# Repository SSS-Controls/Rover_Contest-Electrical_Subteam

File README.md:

# Rover_Contest-Electrical_Subteam
This repo is for the purpose of developing the rover for the UC Davis Space and Satellite Systems Club's participation in the URC rover contest

## Downloading KiCAD
We are currently using *Kicad 10* which (as of the time of this writing) can be found at this link
https://www.kicad.org/download/
**DO NOT USE PREVIOUS VERSIONS. IF YOU DO IT MAY BREAK ALL OF THE WORK YOU DO.**

You'll be able to see the version of KiCAD on the top of the Window (Linux Mint example picture shown)

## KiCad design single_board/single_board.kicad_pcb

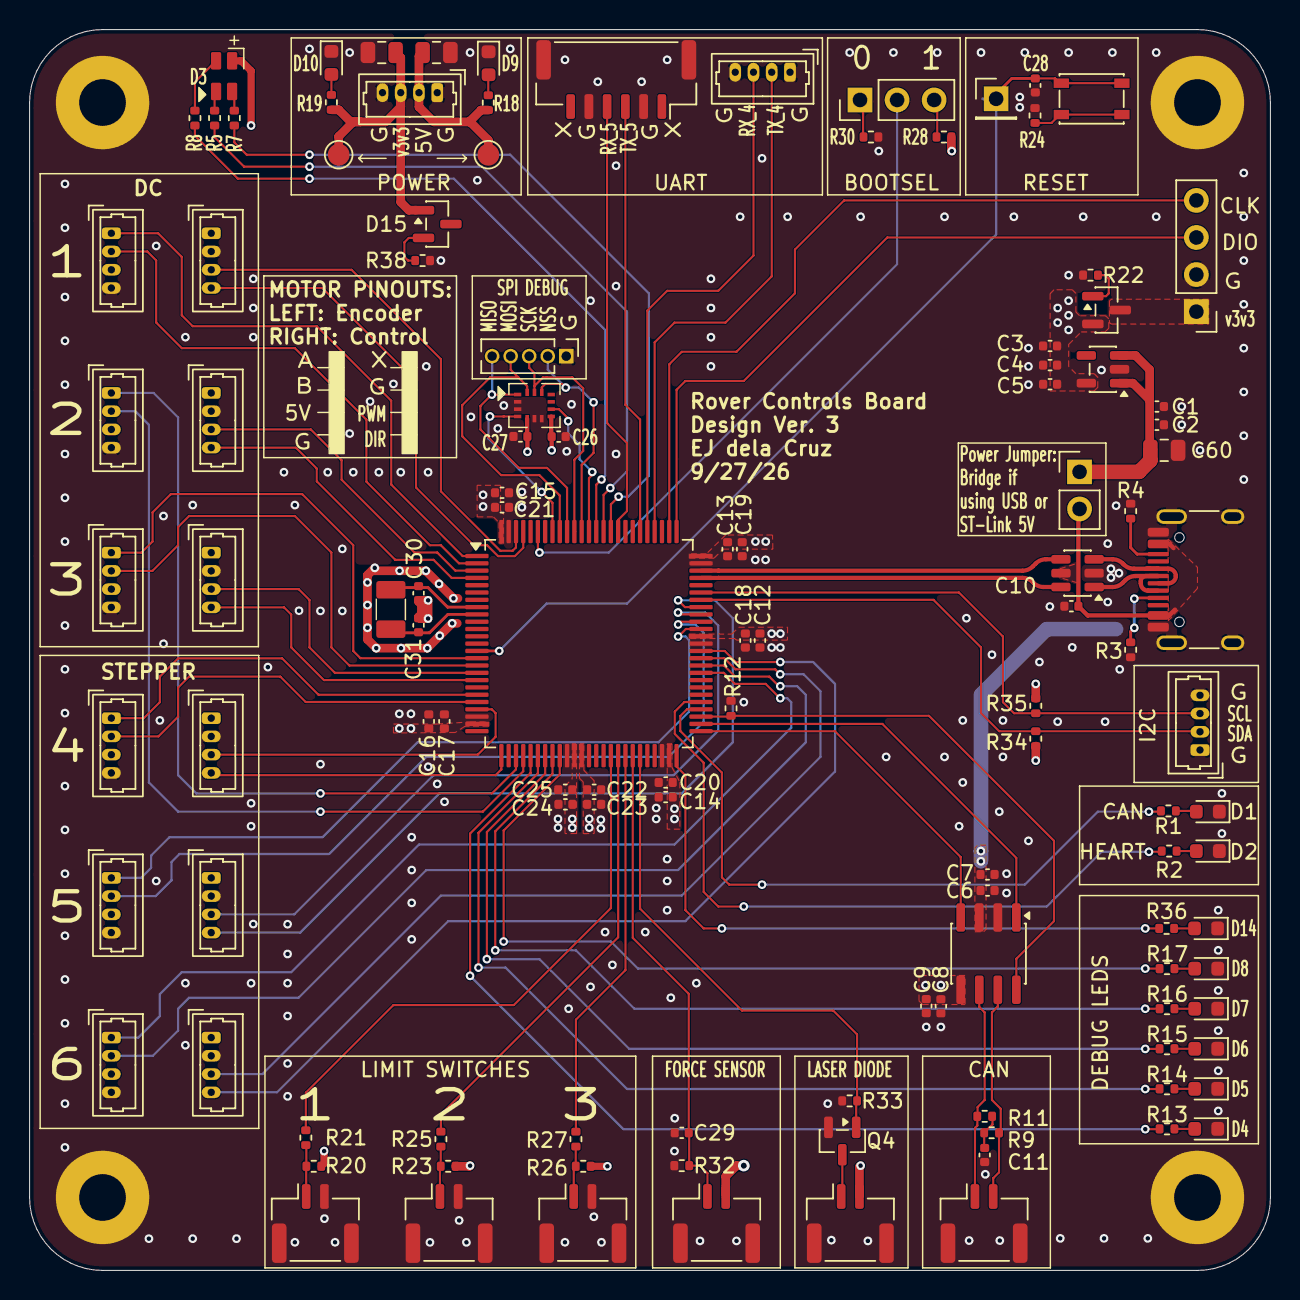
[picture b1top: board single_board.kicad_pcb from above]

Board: 4 copper layers, 85.0 x 85.0 mm, 122 parts (0 on the bottom side), 97 nets.

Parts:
C1, C4, C6, C9, C12, C13, C14, C15, C16, C23, C24: 1uF; C_0402_1005Metric
C2, C3, C7, C8, C10, C17, C18, C19, C20, C21, C25, C26, C27, C28: 100nF; C_0402_1005Metric
C5: 22uF; C_0402_1005Metric
C11, C22, C29: 10nF; C_0402_1005Metric
C30, C31: 10pF; C_0402_1005Metric
C34, C59, C60: 22uF; C_0805_2012Metric
D1, D2, D4, D5, D6, D7, D8, D9, D10, D14: LED; D_0603_1608Metric
D3: FM-B2020RGBA-HG; FM-B2020RGBA-HG Hand Solder
D15: 3.6V; SOT-23
H1, H2, H3, H4: MountingHole_Pad; MountingHole_3.2mm_M3_Pad
J1: Conn_01x02; PinHeader_1x02_P2.54mm_Vertical
J2: USB_C_Receptacle_USB2.0_16P; USB_C_Receptacle_HRO_TYPE-C-31-M-12
J3, J6, J10, J14, J23, J28: JST_GH_H; JST_GH_SM02B-GHS-TB_1x02-1MP_P1.25mm_Horizontal
J4, J7, J8, J11, J12, J13, J15, J16, J19, J21, J22, J24, J25, J26, J27: PB_Vertical; Molex_PicoBlade_53047-0410_1x04_P1.25mm_Vertical
J5: SWD; PinHeader_1x04_P2.54mm_Vertical
J9: RST; PinHeader_1x01_P2.54mm_Vertical
J17: JST-GH; JST_GH_SM06B-GHS-TB_1x06-1MP_P1.25mm_Horizontal
J18: BOOTSEL; PinHeader_1x03_P2.54mm_Vertical
J20: SPI Debug; PinHeader_1x05_P1.27mm_Vertical
Q2: AO3401A; SOT-23
Q4: 2N7002; SOT-23
R1, R2, R12, R13, R14, R15, R16, R17, R18, R19, R22, R24, R28, R30, R33, R36: 10k; R_0402_1005Metric
R3, R4, R34, R35: 5.1k; R_0402_1005Metric
R5, R7, R8, R20, R23, R26: 1k; R_0402_1005Metric
R9, R11: 60; R_0402_1005Metric
R21, R25, R27, R38: 100; R_0402_1005Metric
R32: 1M; R_0402_1005Metric
SW1: Button; SW_SPST_PTS810
TP1, TP2: TestPoint; TestPoint_Pad_D1.5mm
U1: AP2112K-3.3; SOT-23-5
U2: USBLC6-2SC6; SOT-23-6
U3: SOIC-8_3.9x4.9mm_P1.27mm
U4: LSM6DSV
U5: STM32G474VBTx; LQFP-100_14x14mm_P0.5mm
Y1: FC-135; FC-135 Hand Solder

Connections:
5V: C1.1, C2.1, C6.1, C7.1, C34.1, C60.1, J1.1, J4.2, J7.3, J11.3, J15.3, J21.3, J24.3, J26.3, R18.1, TP1.1 (1_1), U1.1 (VIN), U1.3 (EN), U3.3 (VCC)
/BOOT0: J18.2, U5.95 (PB8)
/CAN_DN: J3.1, R11.2, U3.6 (CANL)
/CAN_DP: J3.2, R9.1, U3.7 (CANH)
/CAN_LED: R1.1, U5.54 (PB15)
/CAN_RX: U3.4 (RXD), U5.51 (PB12)
/CAN_STB: R12.1, U3.8 (STB), U5.53 (PB14)
/CAN_TX: U3.1 (TXD), U5.52 (PB13)
/DIR1: J8.4, U5.97 (PE0)
/DIR2: J12.4, U5.4 (PE5)
/DIR3: J16.4, U5.18 (PC3)
/DIR4: J22.4, U5.26 (PA4)
/DIR5: J25.4, U5.68 (PC9)
/DIR6: J27.4, U5.62 (PD15)
/DN: J2.A7 (D-), J2.B7 (D-), U2.1 (I/O1)
/DP: J2.A6 (D+), J2.B6 (D+), U2.3 (I/O2)
/ENC1_A: J7.1, U5.1 (PE2)
/ENC1_B: J7.2, U5.2 (PE3)
/ENC2_A: J11.1, U5.28 (PA6)
/ENC2_B: J11.2, U5.29 (PA7)
/ENC3_A: J15.1, U5.15 (PC0)
/ENC3_B: J15.2, U5.16 (PC1)
/ENC4_A: J21.1, U5.20 (PA0)
/ENC4_B: J21.2, U5.21 (PA1)
/ENC5_A: J24.1, U5.65 (PC6)
/ENC5_B: J24.2, U5.66 (PC7)
/ENC6_A: J26.1, U5.59 (PD12)
/ENC6_B: J26.2, U5.60 (PD13)
/FSR_ADC: C29.1, J23.1, R32.1, U5.44 (PE13)
/HEARTBEAT: R2.1, U5.55 (PD8)
/I2C_SCL: J19.3, R35.2, U5.70 (PA9)
/I2C_SDA: J19.2, R34.2, U5.69 (PA8)
/IMU_MISO: J20.5, U4.1 (SDO/SA0), U5.91 (PB4)
/IMU_MOSI: J20.4, U4.14 (SDA), U5.92 (PB5)
/IMU_NSS: J20.2, U4.12 (CS), U5.89 (PD7)
/IMU_SCK: J20.3, U4.13 (SCL), U5.90 (PB3)
/INT1: U4.4 (INT1), U5.93 (PB6)
/INT2: U4.9 (INT2), U5.88 (PD6)
/LASER_SIG: Q4.1 (G), R33.1, U5.45 (PE14)
/LED1: R13.1, U5.30 (PC4)
/LED2: R14.1, U5.31 (PC5)
/LED3: R15.1, U5.32 (PB0)
/LED4: R16.1, U5.33 (PB1)
/LED5: R17.1, U5.34 (PB2)
/LED6: R36.1, U5.50 (PB11)
/L_SW1: R21.2, U5.41 (PE10)
/L_SW2: R25.2, U5.42 (PE11)
/L_SW3: R27.2, U5.43 (PE12)
/LimitSwitch1: J6.1, R20.2, R21.1
/LimitSwitch2: J10.1, R23.2, R25.1
/LimitSwitch3: J14.1, R26.2, R27.1
/OSC32_IN: C30.1, U5.8 (PC14), Y1.1
/OSC32_OUT: C31.1, U5.9 (PC15), Y1.2
/PWM1: J8.3, U5.98 (PE1)
/PWM2: J12.3, U5.3 (PE4)
/PWM3: J16.3, U5.17 (PC2)
/PWM4: J22.3, U5.22 (PA2)
/PWM5: J25.3, U5.67 (PC8)
/PWM6: J27.3, U5.61 (PD14)
/RST: C28.1, J9.1 (Pin_1_1), SW1.2, U5.14 (PG10)
/SWCLK: J5.4, U5.77 (PA14)
/SWDIO: J5.3, U5.76 (PA13)
/TRI_LED_B: R8.2, U5.87 (PD5)
/TRI_LED_G: R7.2, U5.85 (PD3)
/TRI_LED_R: R5.2, U5.86 (PD4)
/UART4_RX: J13.3, U5.80 (PC11)
/UART4_TX: J13.2, U5.79 (PC10)
/UART5_RX: J17.4, U5.84 (PD2)
/UART5_TX: J17.3, U5.81 (PC12)
/USB-DN: U2.6 (I/O1), U5.72 (PA11)
/USB-DP: U2.4 (I/O2), U5.73 (PA12)
/v3v3IN: J5.1, Q2.3 (D)
/vbus: C10.1, J1.2, J2.A4 (VBUS), J2.A9 (VBUS), J2.B4 (VBUS), J2.B9 (VBUS), U2.5 (VBUS)
GND: C1.2, C2.2, C3.2, C4.2, C5.2, C6.2, C7.2, C8.2, C9.2, C10.2, C11.2, C12.2, C13.2, C14.2, C15.2, C16.2, C17.2, C18.2, C19.2, C20.2, C21.2, C22.2, C23.2, C24.2, C25.2, C26.2, C27.2, C28.2, C29.2, C30.2, C31.2, C34.2, C59.2, C60.2, D1.1 (K), D2.1 (K), D4.1 (K), D5.1 (K), D6.1 (K), D7.1 (K), D8.1 (K), D9.1 (K), D10.1 (K), D14.1 (K), H1.1 (1_1), H2.1 (1_1), H3.1 (1_1), H4.1 (1_1), J2.A1 (GND), J2.A12 (GND), J2.B1 (GND), J2.B12 (GND), J2.SH (SHIELD), J3.MP (MountPin), J4.1, J4.4, J5.2, J6.2, J6.MP (MountPin), J7.4, J8.2, J10.2, J10.MP (MountPin), J11.4, J12.2, J13.1, J13.4, J14.2, J14.MP (MountPin), J15.4, J16.2, J17.2, J17.5, J17.MP (MountPin), J19.1, J19.4, J20.1, J21.4, J22.2, J23.MP (MountPin), J24.4, J25.2, J26.4, J27.2, J28.MP (MountPin), Q4.2 (S), R3.1, R4.1, R12.2, R22.2, R24.2, R30.2, R32.2, R33.2, R38.2, U1.2 (GND), U2.2 (GND), U3.2 (GND), U4.2 (SDx), U4.3 (SCx), U4.6 (GND), U4.7 (GND), U5.23 (VSS), U5.35 (VSSA), U5.48 (VSS), U5.63 (VSS), U5.74 (VSS), U5.99 (VSS)
unnamed: C11.1, R9.2, R11.1
unnamed: D1.2 (A), R1.2
unnamed: D2.2 (A), R2.2
unnamed: D3.2 (BK), R8.1
unnamed: D3.4 (GK), R7.1
unnamed: D3.1 (RK), R5.1
unnamed: D4.2 (A), R13.2
unnamed: D5.2 (A), R14.2
unnamed: D6.2 (A), R15.2
unnamed: D7.2 (A), R16.2
unnamed: D8.2 (A), R17.2
unnamed: D9.2 (A), R18.2
unnamed: D10.2 (A), R19.2
unnamed: D14.2 (A), R36.2
unnamed: D15.2 (A), R38.1
unnamed: J2.A5 (CC1), R3.2
unnamed: J2.B5 (CC2), R4.2
unnamed: J18.1, R30.1
unnamed: J18.3, R28.2
unnamed: J28.1, Q4.3 (D)
unnamed: Q2.1 (G), R22.1
unnamed: R24.1, SW1.1
v3v3: C3.1, C4.1, C5.1, C8.1, C9.1, C12.1, C13.1, C14.1, C15.1, C16.1, C17.1, C18.1, C19.1, C20.1, C21.1, C22.1, C23.1, C24.1, C25.1, C26.1, C27.1, C59.1, D3.3 (A), D15.1 (K), J4.3, J23.2, J28.2, Q2.2 (S), R19.1, R20.1, R23.1, R26.1, R28.1, R34.1, R35.1, TP2.1 (1_1), U1.5 (VOUT), U3.5 (VIO), U4.5 (VDD_IO), U4.8 (VDD), U5.24 (VDD), U5.36 (VREF+), U5.37 (VDDA), U5.49 (VDD), U5.64 (VDD), U5.75 (VDD), U5.100 (VDD)

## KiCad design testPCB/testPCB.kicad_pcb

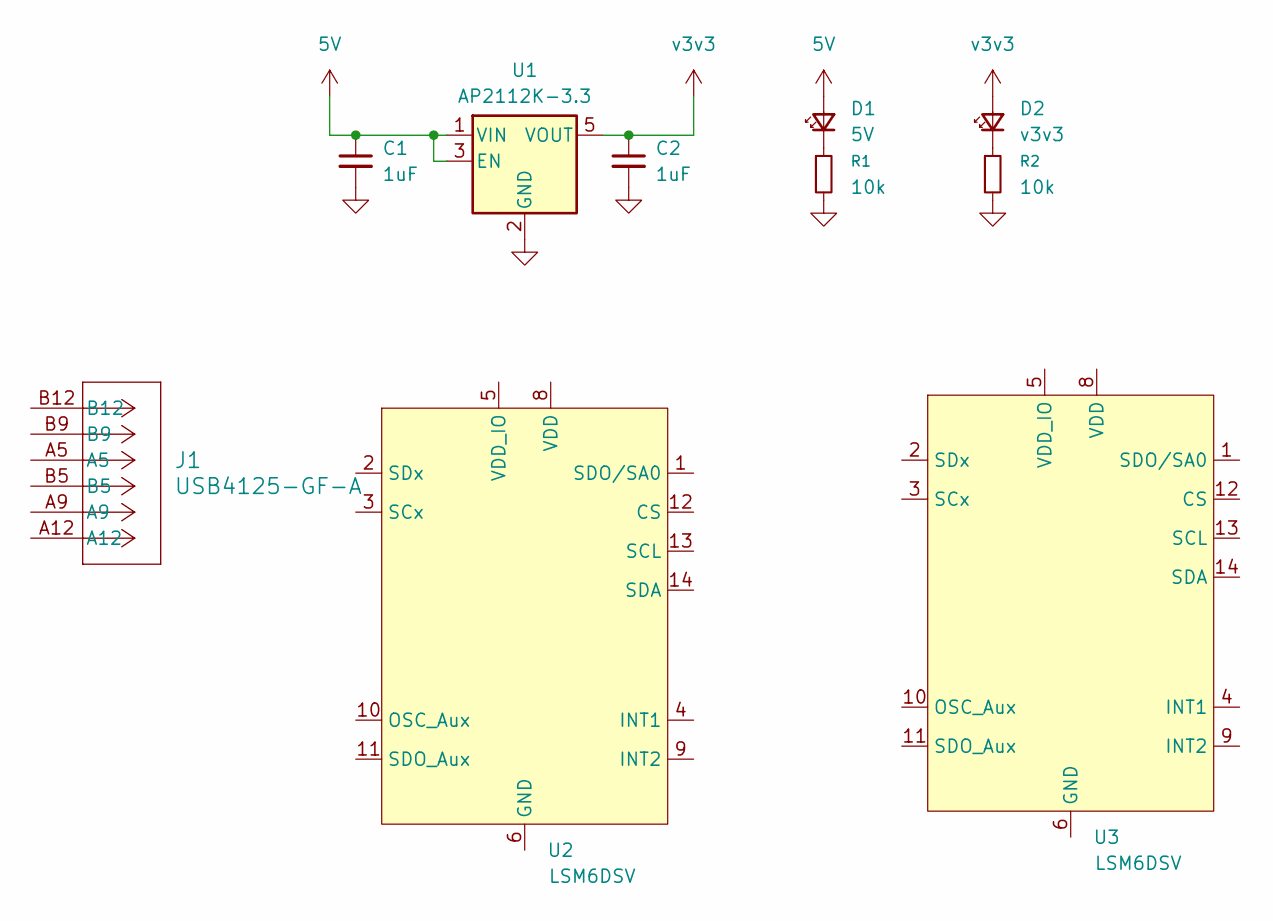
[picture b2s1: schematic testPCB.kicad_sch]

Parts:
C1, C2: 1uF; C_0402_1005Metric
D1: 5V; LED_0402_1005Metric
D2: v3v3; LED_0402_1005Metric
J1: USB4125-GF-A; CONN6_USB4125_GCT
R1, R2: 10k; R_0402_1005Metric
U1: AP2112K-3.3; SOT-23-5
U2, U3: LSM6DSV

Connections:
5V: C1.1, D1.2 (A), U1.1 (VIN), U1.3 (EN)
GND: C1.2, C2.2, R1.2, R2.2, U1.2 (GND)
unnamed: D1.1 (K), R1.1
unnamed: D2.1 (K), R2.1
unnamed: U2.6 (GND), U2.7 (GND)
unnamed: U3.6 (GND), U3.7 (GND)
v3v3: C2.1, D2.2 (A), U1.5 (VOUT)

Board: 2 copper layers, 10 parts (0 on the bottom side), 7 nets, no tracks yet.
